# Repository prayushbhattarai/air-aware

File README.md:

# AirAware

AirAware is a portable particulate matter monitor designed to make air quality visible and understandable. The device measures airborne particles using a Plantower PMS5003 sensor and displays the results through a simple interface powered by an ESP32-C3.

The project combines PCB design, embedded programming, environmental sensing, and classroom education.

Project started: July 2026

## Overview

AirAware was built around a simple question:

What does the air around us actually contain?

Most people cannot see changes in particulate matter concentration as they happen. AirAware provides a portable way to measure those changes and display them in a format that is easy to understand.

The current device measures particulate matter and displays:

* Particle count
* PM2.5 concentration
* A visual air-quality indicator

The interface uses a simple facial indicator to help younger students interpret changes in particle concentration without needing to understand every measurement immediately.

## Hardware

The current AirAware device uses:

* ESP32-C3 SuperMini
* Plantower PMS5003 particulate matter sensor
* 2.0-inch 320 × 240 ST7789 display
* 3.7 V lithium-polymer battery
* Pololu S13V15F5 5 V boost regulator
* Custom 2-layer PCB

## How It Works

The PMS5003 pulls air through its sensing chamber and measures suspended particulate matter.

The sensor sends measurement data to the ESP32-C3 through UART.

The ESP32-C3 processes the sensor readings and updates the ST7789 display with the current particle measurements and visual indicator.

Basic data flow:

PMS5003
↓
UART communication
↓
ESP32-C3
↓
Data processing
↓
ST7789 display

## Display

The interface was designed to stay simple enough for classroom use.

The main screen emphasizes particle count while also showing PM2.5 concentration.

A facial indicator changes based on the measured particle level:

🙂 Lower particle concentration

😐 Moderate particle concentration

☹ Higher particle concentration

The device also includes a startup screen while the PMS5003 completes its initial warm-up period.

## Educational Use

AirAware was designed as both an engineering project and an educational tool.

Students use the devices in small groups to:

* Observe real-time particulate matter measurements
* Compare measurements from different environments
* Test how activities affect airborne particles
* Record experimental data
* Calculate averages
* Compare results between groups
* Discuss possible sources of particulate matter

The goal is to connect environmental science with measurements students collect themselves.

### firmware

Contains the code running on the ESP32-C3.

### hardware/kicad

Contains the editable KiCad project files:

* Schematic
* PCB layout
* KiCad project

### hardware/production

Contains files used to manufacture the PCB, including Gerber and drill files.

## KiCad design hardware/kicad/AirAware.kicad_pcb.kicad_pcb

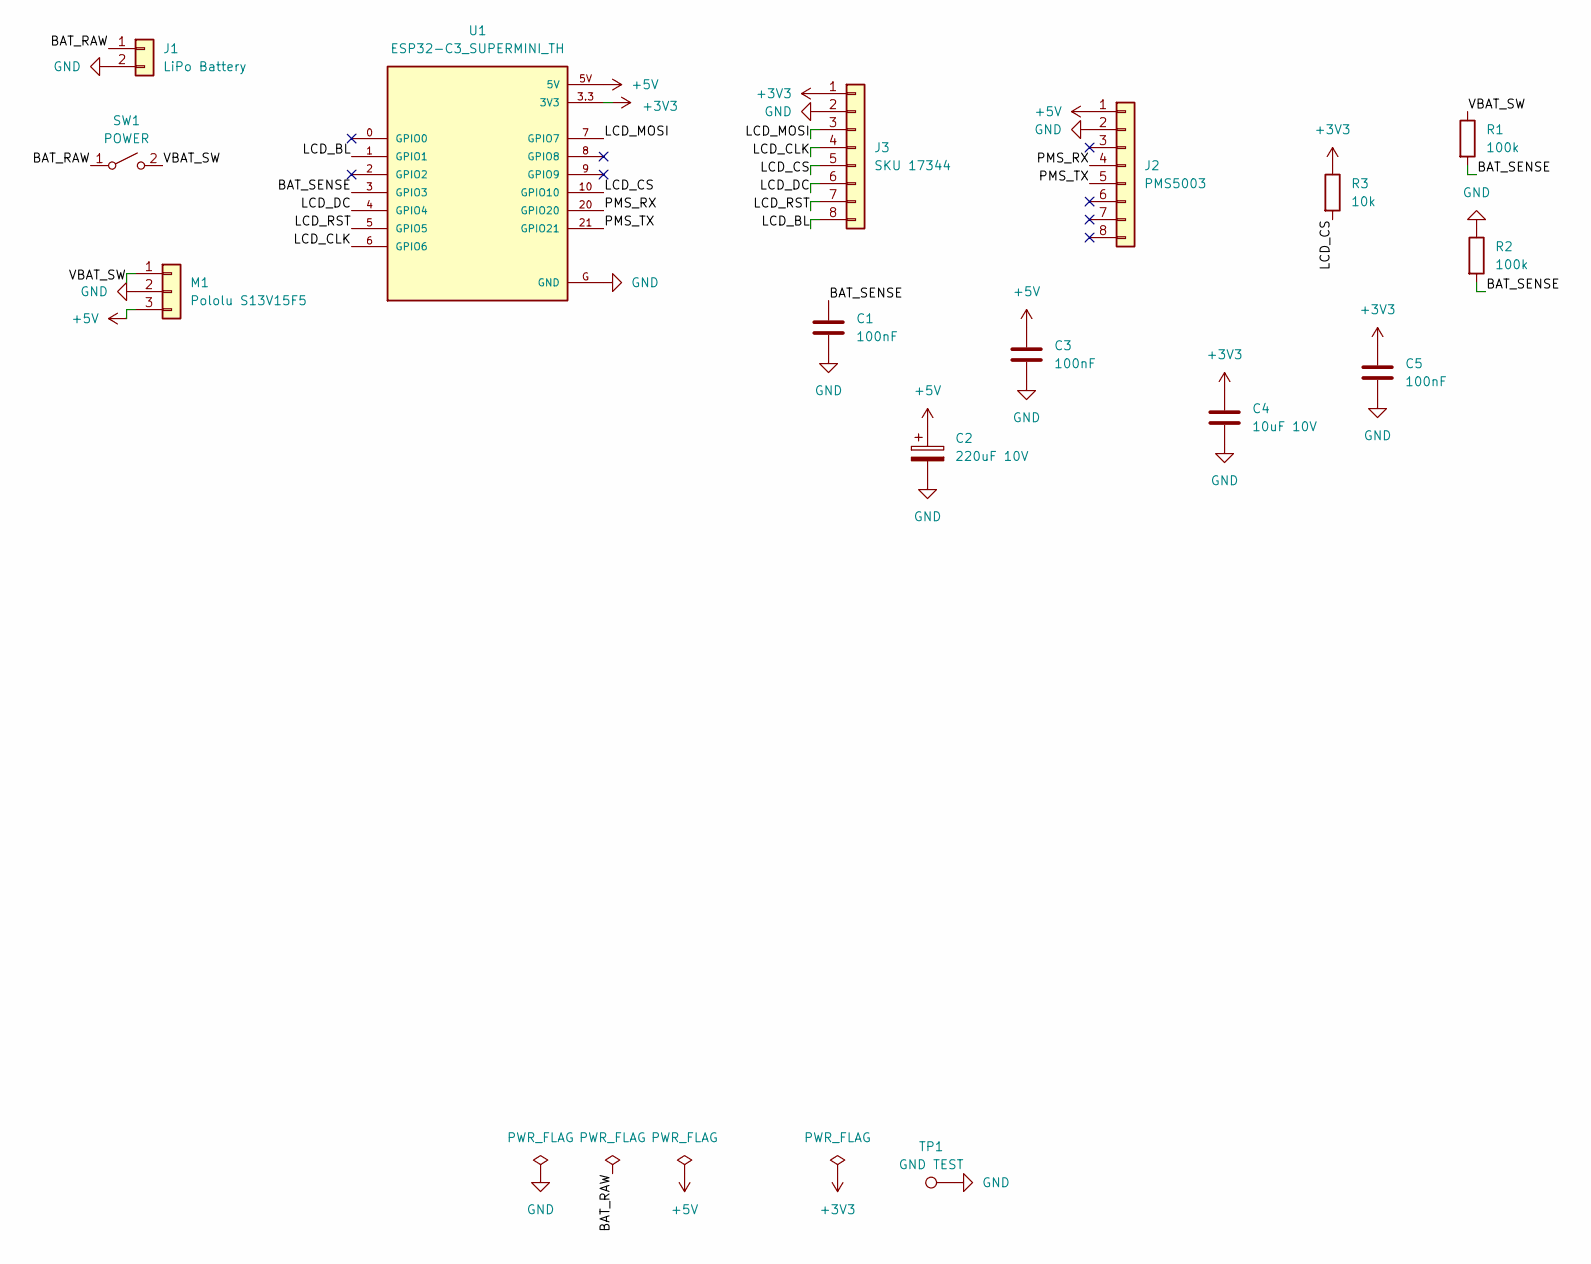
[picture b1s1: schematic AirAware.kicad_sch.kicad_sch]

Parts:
C1, C3, C5: 100nF; C_0805_2012Metric_Pad1.18x1.45mm_HandSolder
C2: 220uF 10V; CP_Radial_D5.0mm_P2.00mm
C4: 10uF 10V; C_1206_3216Metric_Pad1.33x1.80mm_HandSolder
J1: LiPo Battery; JST_PH_B2B-PH-K_1x02_P2.00mm_Vertical
J2: PMS5003; Molex_PicoBlade_53048-0810_1x08_P1.25mm_Horizontal
J3: SKU 17344; JST_PH_S8B-PH-K_1x08_P2.00mm_Horizontal
M1: Pololu S13V15F5; PinHeader_1x03_P2.54mm_Vertical
R1, R2: 100k; R_0805_2012Metric_Pad1.20x1.40mm_HandSolder
R3: 10k; R_0805_2012Metric_Pad1.20x1.40mm_HandSolder
SW1: POWER; SW_CW_GPTS203211B
TP1: GND TEST; TestPoint_Loop_D2.50mm_Drill1.0mm
U1: ESP32-C3_SUPERMINI_TH; MODULE_ESP32-C3_SUPERMINI_TH

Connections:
+3V3: C4.1, C5.1, J3.1, R3.1, U1.3.3 (3V3)
+5V: C2.1, C3.1, J2.1, M1.3, U1.5V
/BAT_RAW: J1.1, SW1.1 (A)
/BAT_SENSE: C1.1, R1.2, R2.2, U1.3 (GPIO3)
/LCD_BL: J3.8, U1.1 (GPIO1)
/LCD_CLK: J3.4, U1.6 (GPIO6)
/LCD_CS: J3.5, R3.2, U1.10 (GPIO10)
/LCD_DC: J3.6, U1.4 (GPIO4)
/LCD_MOSI: J3.3, U1.7 (GPIO7)
/LCD_RST: J3.7, U1.5 (GPIO5)
/PMS_RX: J2.4, U1.20 (GPIO20)
/PMS_TX: J2.5, U1.21 (GPIO21)
/VBAT_SW: M1.1, R1.1, SW1.2 (B)
GND: C1.2, C2.2, C3.2, C4.2, C5.2, J1.2, J2.2, J3.2, M1.2, R2.1, TP1.1, U1.G (GND)

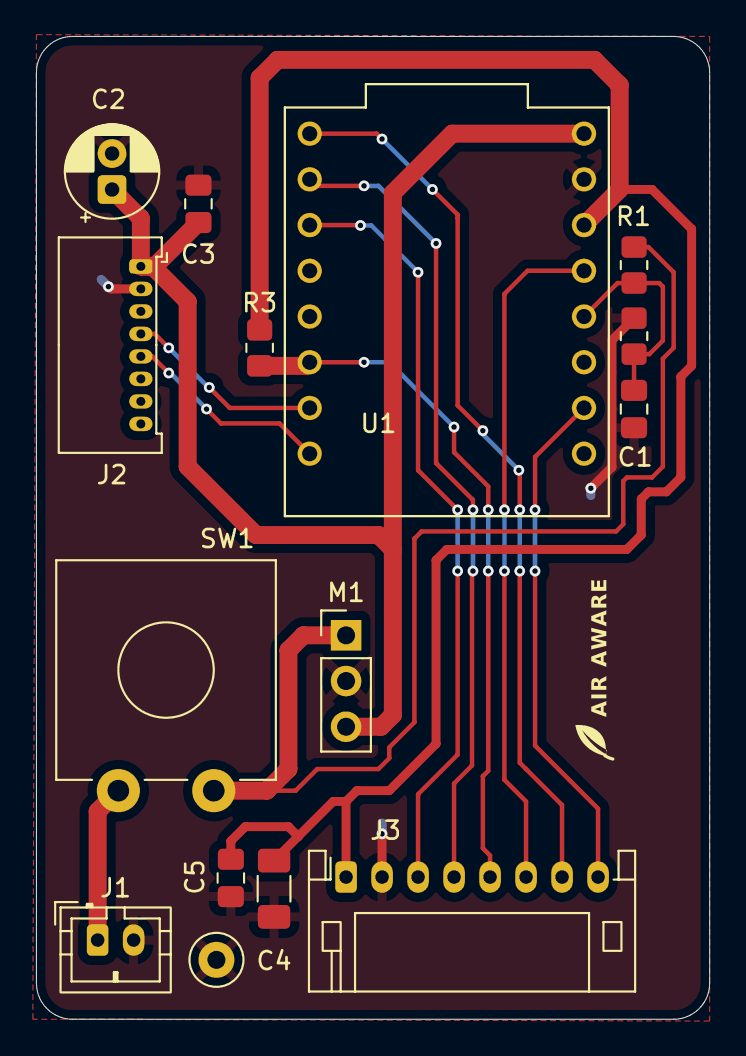
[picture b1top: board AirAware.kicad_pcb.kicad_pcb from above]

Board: 2 copper layers, 37.4 x 54.6 mm, 16 parts (0 on the bottom side), 14 nets.

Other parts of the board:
H2: MountingHole; MountingHole_2.2mm_M2

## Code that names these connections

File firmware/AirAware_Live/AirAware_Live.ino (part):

// Air Aware Nature UI v4 PORTRAIT | ESP32-C3 SuperMini + ST7789 240x320 + PMS5003
// Libraries: Adafruit GFX Library; Adafruit ST7735 and ST7789 Library.
// Board: ESP32C3 Dev Module. USB CDC On Boot: Enabled.
// Working sensor connection: PMS TX -> GPIO21 (ESP receive).
// GPIO20 stays INPUT; this sketch never transmits to the sensor.
#include <Arduino.h>
#include <Adafruit_GFX.h>
#include <Adafruit_ST7789.h>
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#include "driver/uart.h"
#include "driver/gpio.h"

constexpr int LCD_CS = 10, LCD_DC = 4, LCD_MOSI = 7;
constexpr int LCD_CLK = 6, LCD_RST = 5, LCD_BL = 1, PMS_RX = 21;
constexpr uint32_t WARMUP_MS = 30000UL, STALE_MS = 5000UL;
// Example CLASSROOM comparison bands, NOT health limits or AQI categories.
// Count is particles >0.3 micrometers per 0.1 liter, reported by the sensor.
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  config.source_clk = UART_SCLK_DEFAULT;
  requireUart(uart_param_config(UART_NUM_1, &config));
  requireUart(uart_driver_install(UART_NUM_1, 4096, 0, 0, nullptr, 0));
  requireUart(uart_set_pin(UART_NUM_1, UART_PIN_NO_CHANGE, PMS_RX,
                         UART_PIN_NO_CHANGE, UART_PIN_NO_CHANGE));
  requireUart(uart_flush_input(UART_NUM_1));
}
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  gpio_reset_pin(GPIO_NUM_21);
  gpio_set_direction(GPIO_NUM_20, GPIO_MODE_INPUT);
  gpio_set_direction(GPIO_NUM_21, GPIO_MODE_INPUT);
  pinMode(LCD_BL, OUTPUT);
  digitalWrite(LCD_BL, HIGH);
  delay(100);
  SPI.begin(LCD_CLK, -1, LCD_MOSI, LCD_CS);
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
